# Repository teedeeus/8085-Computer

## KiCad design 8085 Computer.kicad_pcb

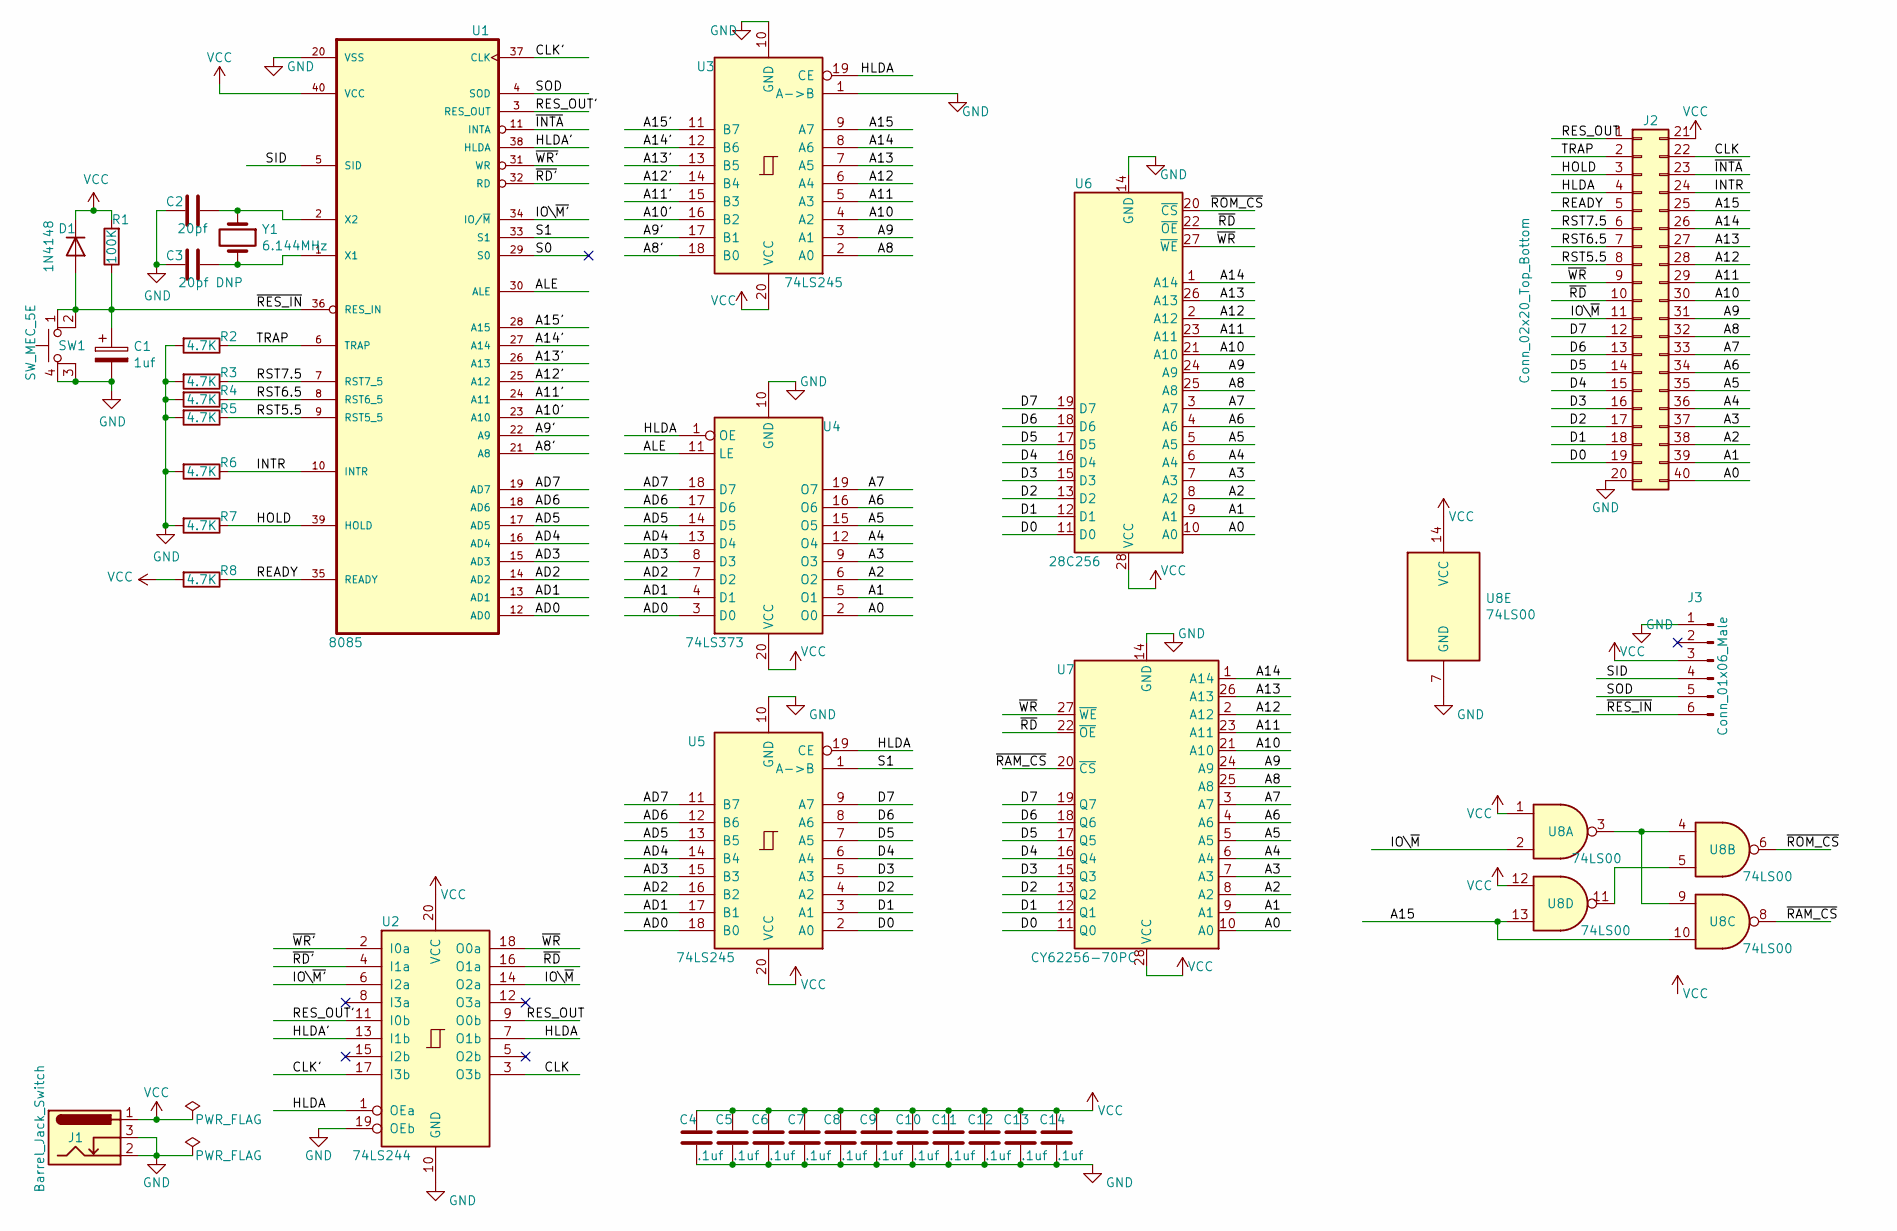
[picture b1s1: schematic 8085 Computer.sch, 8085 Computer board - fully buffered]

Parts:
C1: 1uf; CP_Radial_Tantal_D4.5mm_P2.50mm
C2: 20pf; C_Disc_D3.0mm_W1.6mm_P2.50mm
C3: 20pf DNP; C_Disc_D3.0mm_W1.6mm_P2.50mm
C4, C5, C6, C7, C8, C9, C10, C11, C12, C13, C14: .1uf; C_Disc_D3.0mm_W2.0mm_P2.50mm
D1: 1N4148; D_A-405_P7.62mm_Horizontal
J1: Barrel_Jack_Switch; BarrelJack_Horizontal
J2: Conn_02x20_Top_Bottom; PinHeader_2x20_P2.54mm_Vertical
J3: Conn_01x06_Male; PinHeader_1x06_P2.54mm_Horizontal
R1: 100K; R_Axial_DIN0207_L6.3mm_D2.5mm_P7.62mm_Horizontal
R2, R3, R4, R5, R6, R7, R8: 4.7K; R_Axial_DIN0207_L6.3mm_D2.5mm_P7.62mm_Horizontal
SW1: SW_MEC_5E; SW_TH_Tactile_Omron_B3F-10xx
U1: 8085; DIP-40_W15.24mm
U2: 74LS244; DIP-20_W7.62mm
U3, U5: 74LS245; DIP-20_W7.62mm
U4: 74LS373; DIP-20_W7.62mm
U6: 28C256; DIP-28_W15.24mm
U7: CY62256-70PC; DIP-28_W15.24mm
U8: 74LS00; DIP-16_W7.62mm
Y1: 6.144MHz; Crystal_HC33-U_Vertical

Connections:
/A0: J2.40, U4.2 (O0), U6.10 (A0), U7.10 (A0)
/A1: J2.39, U4.5 (O1), U6.9 (A1), U7.9 (A1)
/A2: J2.38, U4.6 (O2), U6.8 (A2), U7.8 (A2)
/A3: J2.37, U4.9 (O3), U6.7 (A3), U7.7 (A3)
/A4: J2.36, U4.12 (O4), U6.6 (A4), U7.6 (A4)
/A5: J2.35, U4.15 (O5), U6.5 (A5), U7.5 (A5)
/A6: J2.34, U4.16 (O6), U6.4 (A6), U7.4 (A6)
/A7: J2.33, U4.19 (O7), U6.3 (A7), U7.3 (A7)
/A8: J2.32, U3.2 (A0), U6.25 (A8), U7.25 (A8)
/A8': U1.21 (A8), U3.18 (B0)
/A9: J2.31, U3.3 (A1), U6.24 (A9), U7.24 (A9)
/A9': U1.22 (A9), U3.17 (B1)
/A10: J2.30, U3.4 (A2), U6.21 (A10), U7.21 (A10)
/A10': U1.23 (A10), U3.16 (B2)
/A11: J2.29, U3.5 (A3), U6.23 (A11), U7.23 (A11)
/A11': U1.24 (A11), U3.15 (B3)
/A12: J2.28, U3.6 (A4), U6.2 (A12), U7.2 (A12)
/A12': U1.25 (A12), U3.14 (B4)
/A13: J2.27, U3.7 (A5), U6.26 (A13), U7.26 (A13)
/A13': U1.26 (A13), U3.13 (B5)
/A14: J2.26, U3.8 (A6), U6.1 (A14), U7.1 (A14)
/A14': U1.27 (A14), U3.12 (B6)
/A15: J2.25, U3.9 (A7), U8.10, U8.13
/A15': U1.28 (A15), U3.11 (B7)
/AD0: U1.12 (AD0), U4.3 (D0), U5.18 (B0)
/AD1: U1.13 (AD1), U4.4 (D1), U5.17 (B1)
/AD2: U1.14 (AD2), U4.7 (D2), U5.16 (B2)
/AD3: U1.15 (AD3), U4.8 (D3), U5.15 (B3)
/AD4: U1.16 (AD4), U4.13 (D4), U5.14 (B4)
/AD5: U1.17 (AD5), U4.14 (D5), U5.13 (B5)
/AD6: U1.18 (AD6), U4.17 (D6), U5.12 (B6)
/AD7: U1.19 (AD7), U4.18 (D7), U5.11 (B7)
/ALE: U1.30 (ALE), U4.11 (LE)
/CLK: J2.22, U2.3 (O3b)
/CLK': U1.37 (CLK), U2.17 (I3b)
/D0: J2.19, U5.2 (A0), U6.11 (D0), U7.11 (Q0)
/D1: J2.18, U5.3 (A1), U6.12 (D1), U7.12 (Q1)
/D2: J2.17, U5.4 (A2), U6.13 (D2), U7.13 (Q2)
/D3: J2.16, U5.5 (A3), U6.15 (D3), U7.15 (Q3)
/D4: J2.15, U5.6 (A4), U6.16 (D4), U7.16 (Q4)
/D5: J2.14, U5.7 (A5), U6.17 (D5), U7.17 (Q5)
/D6: J2.13, U5.8 (A6), U6.18 (D6), U7.18 (Q6)
/D7: J2.12, U5.9 (A7), U6.19 (D7), U7.19 (Q7)
/HLDA: J2.4, U2.1 (OEa), U2.7 (O1b), U3.19 (CE), U4.1 (OE), U5.19 (CE)
/HLDA': U1.38 (HLDA), U2.13 (I1b)
/HOLD: J2.3, R7.1, U1.39 (HOLD)
/INTR: J2.24, R6.1, U1.10 (INTR)
/IO\~M: J2.11, U2.14 (O2a), U8.2
/IO\~M': U1.34 (IO/~M), U2.6 (I2a)
/READY: J2.5, R8.1, U1.35 (READY)
/RES_OUT: J2.1, U2.9 (O0b)
/RES_OUT': U1.3 (RES_OUT), U2.11 (I0b)
/RST5.5: J2.8, R5.1, U1.9 (RST5_5)
/RST6.5: J2.7, R4.1, U1.8 (RST6_5)
/RST7.5: J2.6, R3.1, U1.7 (RST7_5)
/S0: U1.29 (S0)
/S1: U1.33 (S1), U5.1 (A->B)
/SID: J3.4, U1.5 (SID)
/SOD: J3.5, U1.4 (SOD)
/TRAP: J2.2, R2.1, U1.6 (TRAP)
/~INTA: J2.23, U1.11 (INTA)
/~RAM_CS: U7.20 (~CS), U8.8
/~RD: J2.10, U2.16 (O1a), U6.22 (~OE), U7.22 (~OE)
/~RD': U1.32 (RD), U2.4 (I1a)
/~RES_IN: C1.1, D1.2 (A), J3.6, R1.1, SW1.1, SW1.2, U1.36 (RES_IN)
/~ROM_CS: U6.20 (~CS), U8.6
/~WR: J2.9, U2.18 (O0a), U6.27 (~WE), U7.27 (~WE)
/~WR': U1.31 (WR), U2.2 (I0a)
GND: C1.2, C2.2, C3.2, C4.2, C5.2, C6.2, C7.2, C8.2, C9.2, C10.2, C11.2, C12.2, C13.2, C14.2, J1.2, J1.3, J2.20, J3.1, R2.2, R3.2, R4.2, R5.2, R6.2, R7.2, SW1.3 (K), SW1.4 (A), U1.20 (VSS), U2.10 (GND), U2.19 (OEb), U3.1 (A->B), U3.10 (GND), U4.10 (GND), U5.10 (GND), U6.14 (GND), U7.14 (GND), U8.7 (GND)
unnamed: C2.1, U1.2 (X2), Y1.1
unnamed: C3.1, U1.1 (X1), Y1.2
unnamed: U8.3, U8.4, U8.9
unnamed: U8.5, U8.11
VCC: C4.1, C5.1, C6.1, C7.1, C8.1, C9.1, C10.1, C11.1, C12.1, C13.1, C14.1, D1.1 (K), J1.1, J2.21, J3.3, R1.2, R8.2, U1.40 (VCC), U2.20 (VCC), U3.20 (VCC), U4.20 (VCC), U5.20 (VCC), U6.28 (VCC), U7.28 (VCC), U8.1, U8.12, U8.14 (VCC)

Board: 2 copper layers, 36 parts (0 on the bottom side), 73 nets, no tracks yet.

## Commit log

2020-11-24 Add files via upload
    Initial commit
2020-11-25 Starting board layout
